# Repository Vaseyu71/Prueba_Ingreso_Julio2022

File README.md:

# Prueba_Ingreso_Julio2022

La prueba consta de dos partes, una primera parte enfoncada mucho al diseño, interpretación de circuitos electronicos, y una segunda parte mas en logica y programación.

El tiempo de entrega sera de 48Horas empezando desde el dia Sabado 30 de Junio a las 07:00:00 y finalizando el Lunes 01 de Agosto a las 07:00:00 se deberan de adjuntar al presente repositorio todos lo documentos, codigo e información pertinente utilizada para la solución de cada uno de los problemas planteados a si como las pruebas teoricas.

Para la solucion de cada uno de los problemas el aspirante es libre de escoger el hardware, lenguaje de programación que mejor se le acomode.

# Solucion de la prueba
## Paso 1. Clone el repositorio
## Paso 2. Cree una nueva rama con el siguiente formato
    NombrePrimerApellido
  Para probar que todo este bien, una vez clonado el repositorio y creada la rama puede realizar un push y corroborar todos sus cambios.
  
## Paso. Al finalizar el examen realice de nuevo un push a su rama. Recuerde se calificara solamente el ultimo commit realizado tengalo muy presente.

# Resultado
## Prueba 01
Presenta una buena capacidad para interpretar y analizar circuitos,  a espera de archivo PDF con esquematico de los puntos 2 y 3.

## Prueba 02
- Conocimiento en linux demostrados en aplicaciónes basicas
- Conocimiento en microcontroladores comerciales ESP32 y ESP8266
- Buena interpretación y analisis de problemas para solución.

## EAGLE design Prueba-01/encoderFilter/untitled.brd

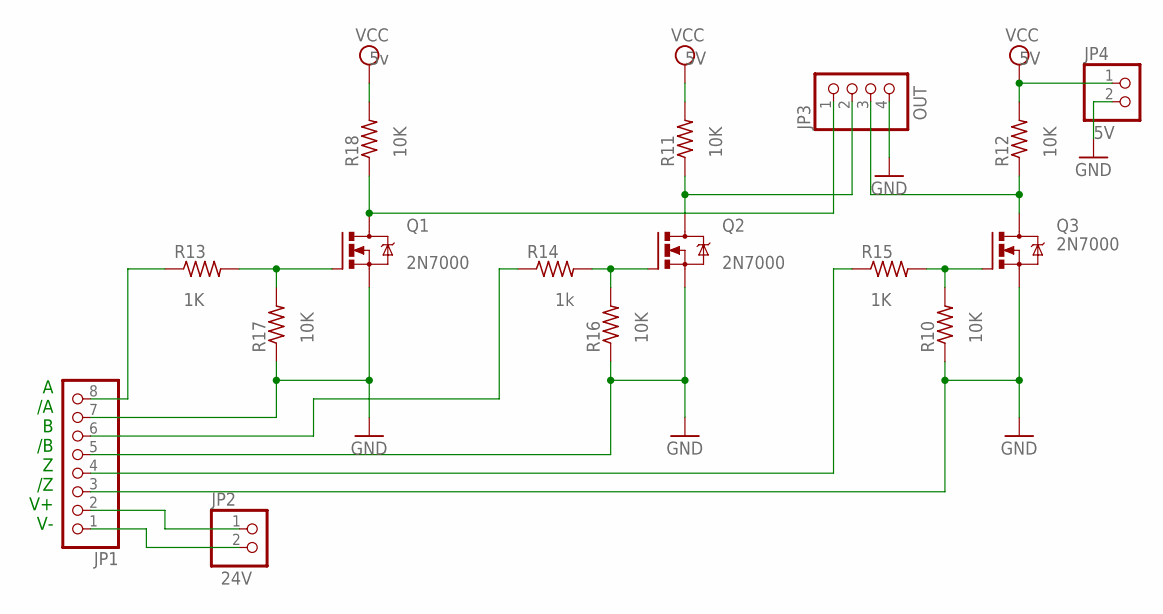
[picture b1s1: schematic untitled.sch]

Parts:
JP1: PINHD-1X8; 1X08
JP2, JP4: PINHD-1X2; 1X02
JP3: PINHD-1X4; 1X04
Q1, Q2, Q3: IRF540; TO220BV
R10, R11, R12, R13, R14, R15, R16, R17, R18: R-US_M0805; M0805

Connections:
GND: JP1.3, JP1.5, JP1.7, JP3.4, JP4.2, Q1.S, Q2.S, Q3.S, R10.1, R16.1, R17.1
unnamed: JP3.3, Q3.D, R12.1
unnamed: Q3.G, R10.2, R15.2
unnamed: JP3.2, Q2.D, R11.1
unnamed: Q2.G, R14.2, R16.2
unnamed: Q1.G, R13.2, R17.2
unnamed: JP3.1, Q1.D, R18.1
unnamed: JP1.8, R13.1
unnamed: JP1.6, R14.1
unnamed: JP1.4, R15.1
unnamed: JP1.2, JP2.1
unnamed: JP1.1, JP2.2
VCC: JP4.1, R11.2, R12.2, R18.2

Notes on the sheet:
A /A B /B Z /Z V+ V-

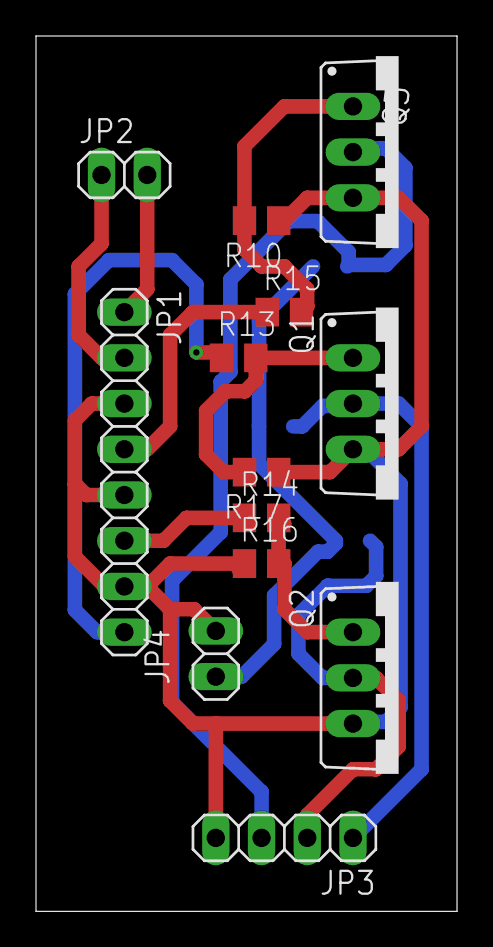
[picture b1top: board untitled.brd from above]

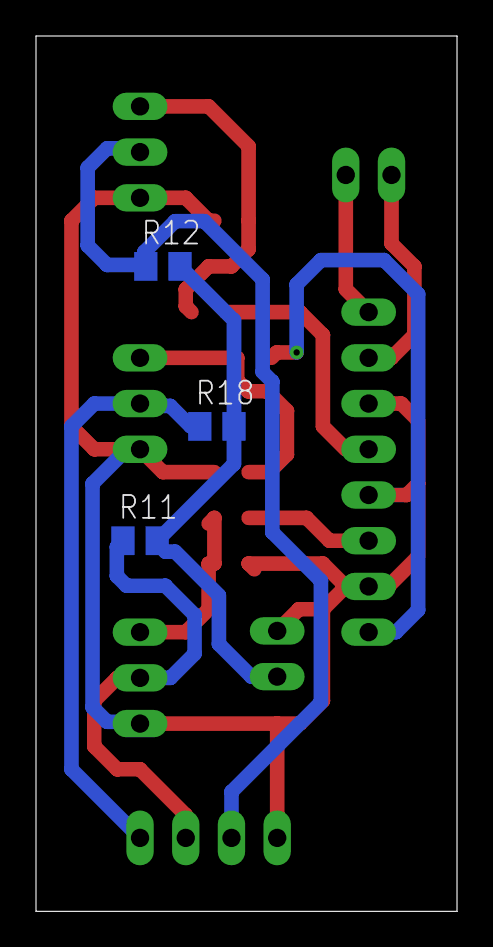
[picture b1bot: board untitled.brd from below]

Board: 2 copper layers, 23.4 x 48.6 mm, 16 parts (3 on the bottom side), 13 nets.

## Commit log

2022-07-29 Agregando Archivos de pruebas
2022-07-31 starting to solve
2022-08-01 adding last points solved
2022-08-01 update brd
